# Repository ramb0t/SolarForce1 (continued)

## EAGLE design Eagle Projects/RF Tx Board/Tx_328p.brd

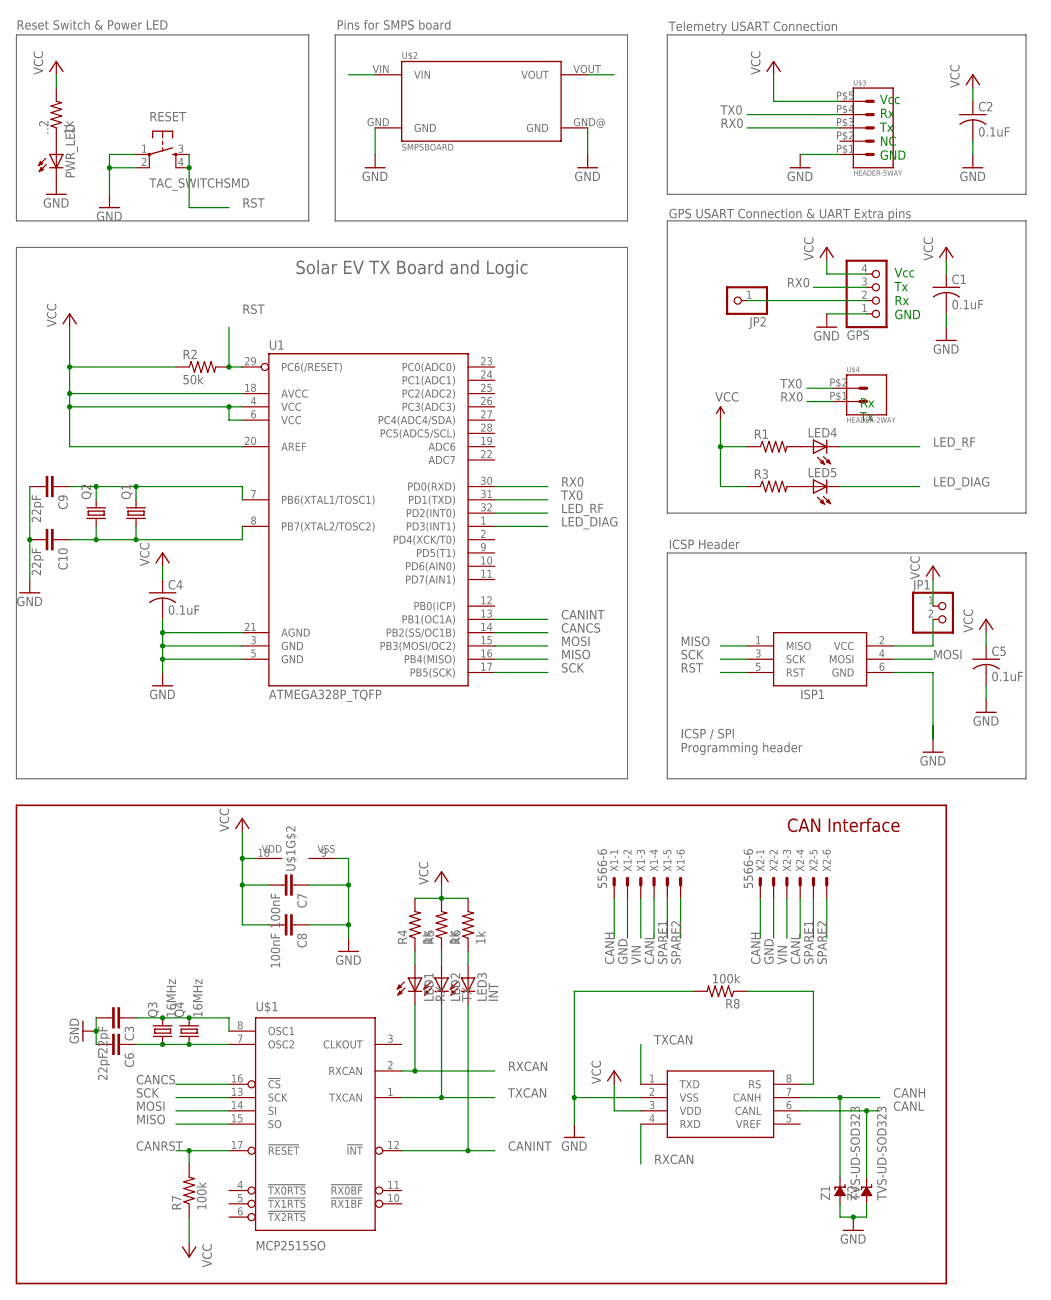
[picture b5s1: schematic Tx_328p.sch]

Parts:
..2: 1k; M0805
C1, C2, C4, C5: 0.1uF; C0805
C3, C6, C9, C10: 22pF; C0805K
C7, C8: 100nF; C0805K
GPS: PINHD-1X4; 1X04
ISP1: AVRISP-BOX
JP1: PINHD-1X2; 1X02
JP2: PINHD-1X1; 1X01
LED1: RX; CHIP-LED0805
LED2: TX; CHIP-LED0805
LED3: INT; CHIP-LED0805
LED4, LED5: LEDSML0805; SML0805
PWR_LED: LEDCHIP-LED0805; CHIP-LED0805
Q1: CRYSTALHC49S; HC49/S
Q2: CRYSTALSM49; SM49
Q3: 16MHz; HC49/S
Q4: 16MHz; HC49UP
R1, R3: R-US_M0805; M0805
R2: 50k; M0805
R4, R5, R6: 1k; R0805
R7, R8: 100k; R0805
RESET: TAC_SWITCHSMD; TACTILE-SWITCH-SMD
U1: ATMEGA328P_TQFP; TQFP32-08
U2: MCP2551; SO08
U$1: MCP2515SO; SO-18W
U$2: SMPSBOARD
U$3: HEADER-5WAY; 1744426-5
U$4: HEADER-2WAY; 1744426-2
X1, X2: 5566-6
Z1, Z2: TVS-UD-SOD323; SOD323

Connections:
CANCS: U1.14 (PB2(SS/OC1B)), U$1.16 (!CS)
CANH: U2.7 (CANH), X1.1, X2.1, Z1.C
CANINT: LED3.C, U1.13 (PB1(OC1A)), U$1.12 (!INT)
CANL: U2.6 (CANL), X1.4, X2.4, Z2.C
CANRST: R7.2, U$1.17 (!RESET)
CANSTBY: R8.1, U2.8 (RS)
GND: C1.2, C2.2, C3.2, C4.2, C5.2, C6.2, C7.1, C8.1, C9.2, C10.2, GPS.1, ISP1.6 (GND), PWR_LED.C, R8.2, RESET.1, RESET.2, U1.3 (GND), U1.5 (GND), U1.21 (AGND), U2.2 (VSS), U$1.9 (VSS), U$2.GND, U$2.GND@ (GND), U$3.P$1, X1.2, X2.2, Z1.A, Z2.A
LED_DIAG: LED5.C, U1.1 (PD3(INT1))
LED_RF: LED4.C, U1.32 (PD2(INT0))
MISO: ISP1.1 (MISO), U1.16 (PB4(MISO)), U$1.15 (SO)
MOSI: ISP1.4 (MOSI), U1.15 (PB3(MOSI/OC2)), U$1.14 (SI)
unnamed: C9.1, Q1.2, Q2.2, U1.7 (PB6(XTAL1/TOSC1))
unnamed: C10.1, Q1.1, Q2.1, U1.8 (PB7(XTAL2/TOSC2))
unnamed: GPS.2, JP2.1
unnamed: LED4.A, R1.2
unnamed: LED5.A, R3.2
unnamed: ..2.1, PWR_LED.A
unnamed: LED1.A, R4.1
unnamed: LED2.A, R5.1
unnamed: LED3.A, R6.1
unnamed: C3.1, Q3.2, Q4.2, U$1.8 (OSC1)
unnamed: C6.1, Q3.1, Q4.1, U$1.7 (OSC2)
unnamed: ISP1.2 (VCC), JP1.2
RST: ISP1.5 (RST), R2.2, RESET.3, RESET.4, U1.29 (PC6(/RESET))
RX0: GPS.3, U1.30 (PD0(RXD)), U$3.P$3, U$4.P$1
RXCAN: LED1.C, U2.4 (RXD), U$1.2 (RXCAN)
SCK: ISP1.3 (SCK), U1.17 (PB5(SCK)), U$1.13 (SCK)
SPARE1: X1.5, X2.5
SPARE2: X1.6, X2.6
TX0: U1.31 (PD1(TXD)), U$3.P$4, U$4.P$2
TXCAN: LED2.C, U2.1 (TXD), U$1.1 (TXCAN)
VCC: ..2.2, C1.1, C2.1, C4.1, C5.1, C7.2, C8.2, GPS.4, JP1.1, R1.1, R2.1, R3.1, R4.2, R5.2, R6.2, R7.1, U1.4 (VCC), U1.6 (VCC), U1.18 (AVCC), U1.20 (AREF), U2.3 (VDD), U$1.18 (VDD), U$2.VOUT, U$3.P$5
VIN: U$2.VIN, X1.3, X2.3

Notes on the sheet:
Vcc Rx Tx NC GND
Vcc Tx Rx GND
Rx Tx
ICSP / SPI Programming header
Reset Switch & Power LED
Pins for SMPS board
Telemetry USART Connection
GPS USART Connection & UART Extra pins
ICSP Header
Solar EV TX Board and Logic
CAN Interface

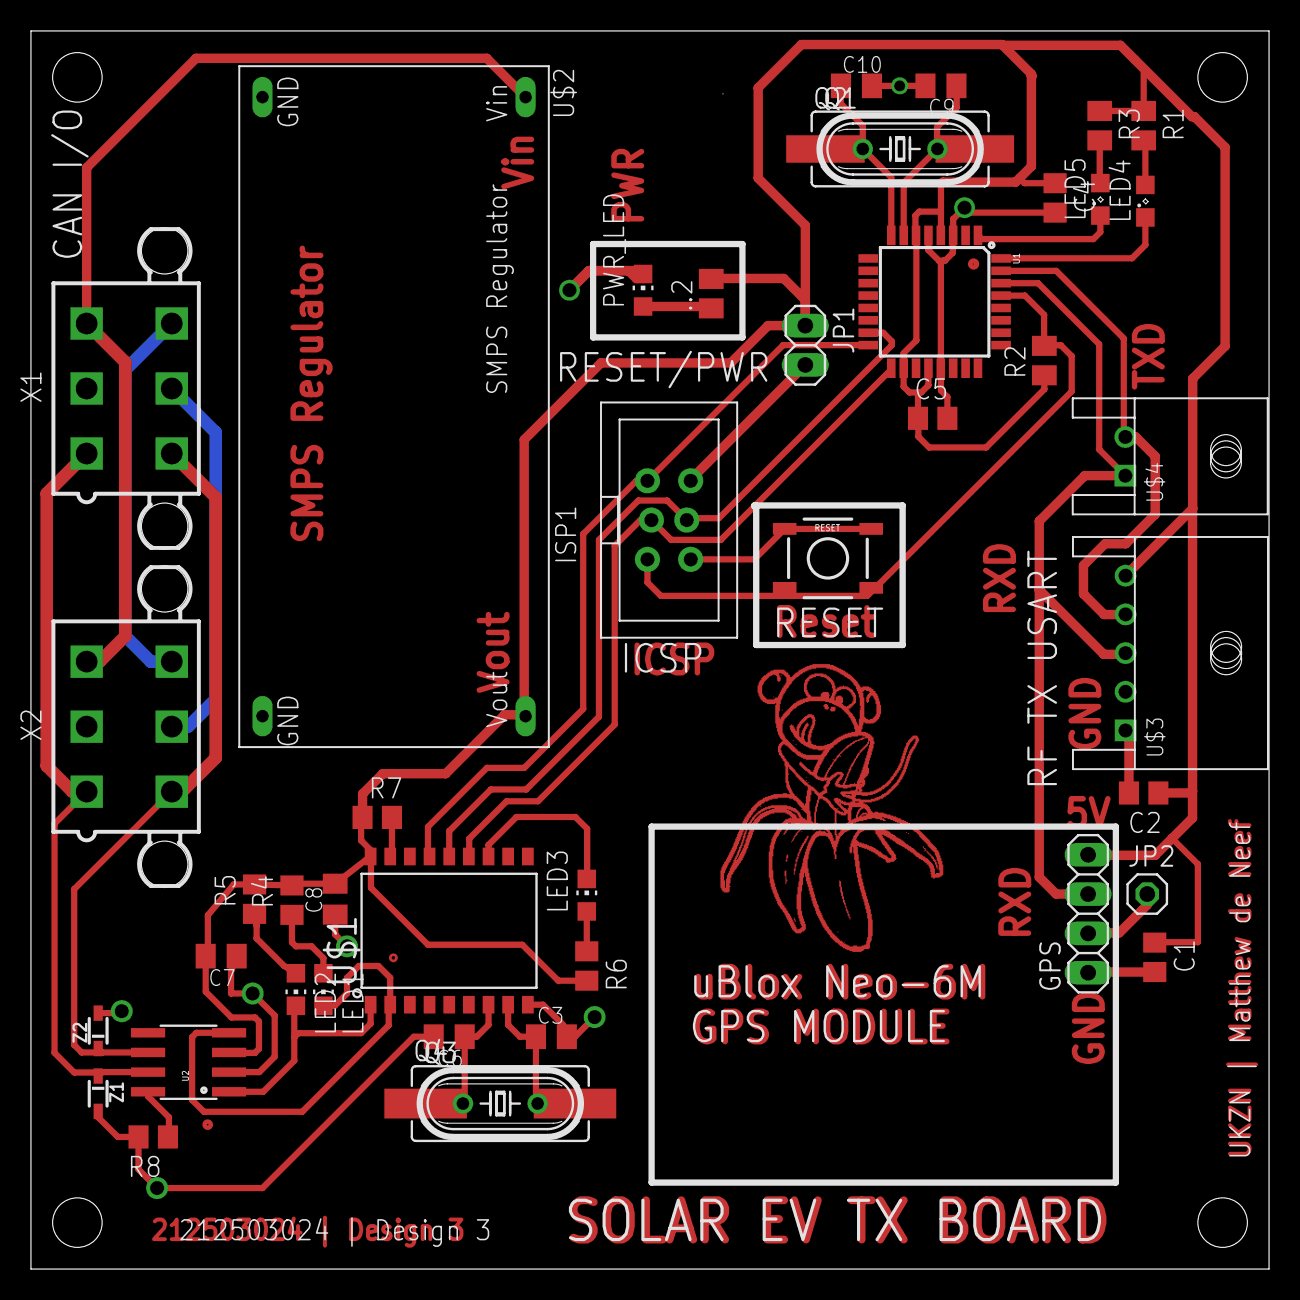
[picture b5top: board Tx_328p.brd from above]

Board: 2 copper layers, 80.0 x 80.0 mm, 44 parts (0 on the bottom side), 33 nets.

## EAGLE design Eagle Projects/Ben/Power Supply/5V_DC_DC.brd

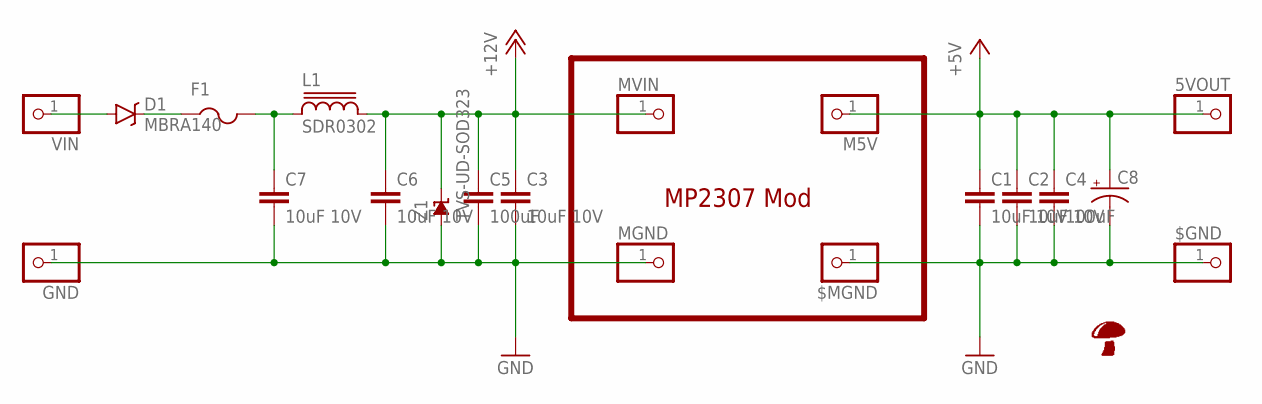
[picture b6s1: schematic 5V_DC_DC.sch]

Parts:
5VOUT: PINHD-1X1; 1X01
$GND: PINHD-1X1; 1X01
$MGND: PINHD-1X1; 1X01
C1, C2, C3, C6, C7: 10uF 10V; C0805
C4, C5: 100uF; C1206
C8: CPOL-USD; PANASONIC_D
D1: MBRA140; SMA-DIODE
F1: PTCFUSE-1812; 1812
GND: PINHD-1X1; 1X01
L1: SDR0302
M5V: PINHD-1X1; 1X01
MGND: PINHD-1X1; 1X01
MVIN: PINHD-1X1; 1X01
U$1: SHROOM5MM; SHROOM
VIN: PINHD-1X1; 1X01
Z1: TVS-UD-SOD323; SOD323

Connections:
+5V: 5VOUT.1, C1.1, C2.1, C4.1, C8.+, M5V.1
+12V: C3.1, C5.1, C6.1, L1.2, MVIN.1, Z1.C
GND: $GND.1, $MGND.1, C1.2, C2.2, C3.2, C4.2, C5.2, C6.2, C7.2, C8.-, GND.1, MGND.1, Z1.A
unnamed: C7.1, F1.2, L1.1
unnamed: D1.C, F1.1
unnamed: D1.A, VIN.1

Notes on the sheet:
MP2307 Mod

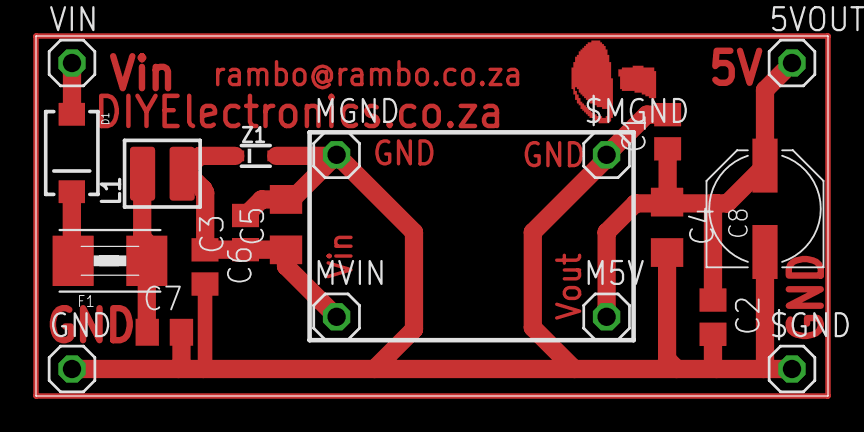
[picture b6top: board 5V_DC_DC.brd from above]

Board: 2 copper layers, 44.0 x 20.0 mm, 21 parts (0 on the bottom side), 6 nets.

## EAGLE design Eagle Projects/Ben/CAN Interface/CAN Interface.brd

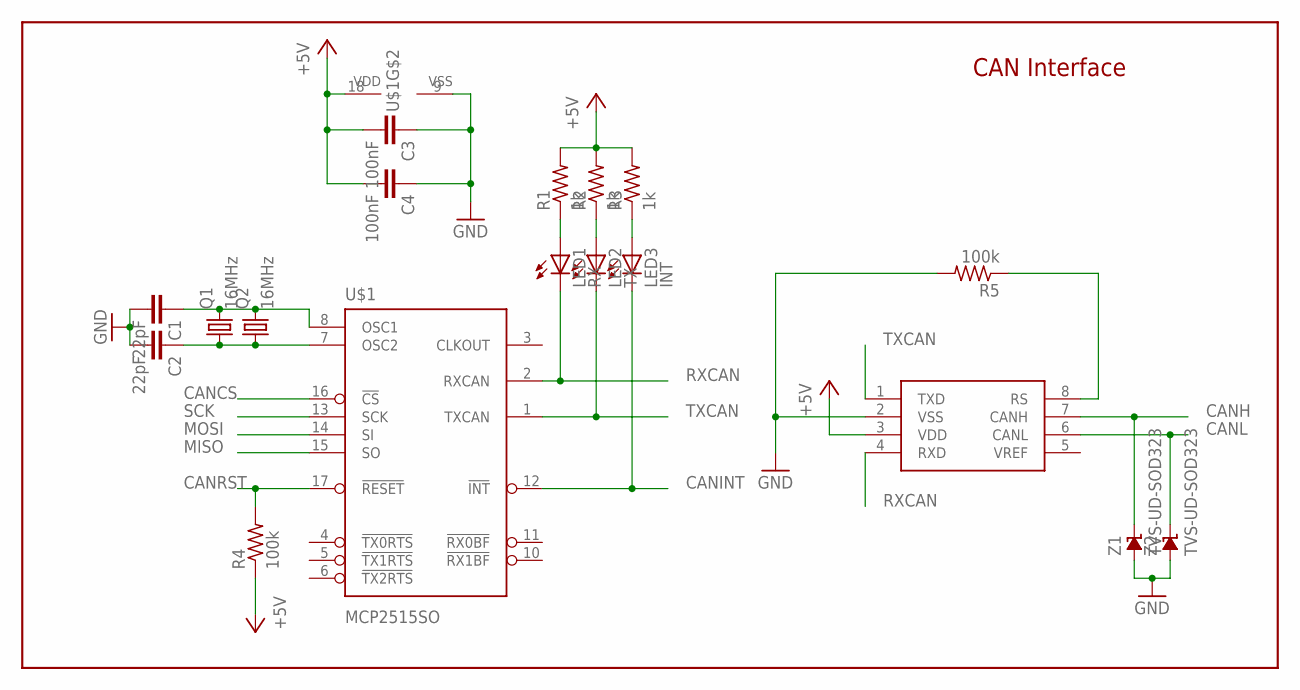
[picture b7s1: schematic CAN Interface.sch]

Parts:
C1, C2: 22pF; C0805K
C3, C4: 100nF; C0805K
LED1: RX; CHIP-LED0805
LED2: TX; CHIP-LED0805
LED3: INT; CHIP-LED0805
Q1: 16MHz; HC49/S
Q2: 16MHz; HC49UP
R1, R2, R3: 1k; R0805
R4, R5: 100k; R0805
U1: MCP2551; SO08
U$1: MCP2515SO; SO-18W
Z1, Z2: TVS-UD-SOD323; SOD323

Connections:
+5V: C3.2, C4.2, R1.2, R2.2, R3.2, R4.1, U1.3 (VDD), U$1.18 (VDD)
CANCS: U$1.16 (!CS)
CANH: U1.7 (CANH), Z1.C
CANINT: LED3.C, U$1.12 (!INT)
CANL: U1.6 (CANL), Z2.C
CANRST: R4.2, U$1.17 (!RESET)
CANSTBY: R5.1, U1.8 (RS)
GND: C1.2, C2.2, C3.1, C4.1, R5.2, U1.2 (VSS), U$1.9 (VSS), Z1.A, Z2.A
MISO: U$1.15 (SO)
MOSI: U$1.14 (SI)
unnamed: C2.1, Q1.1, Q2.1, U$1.7 (OSC2)
unnamed: C1.1, Q1.2, Q2.2, U$1.8 (OSC1)
unnamed: LED1.A, R1.1
unnamed: LED2.A, R2.1
unnamed: LED3.A, R3.1
RXCAN: LED1.C, U1.4 (RXD), U$1.2 (RXCAN)
SCK: U$1.13 (SCK)
TXCAN: LED2.C, U1.1 (TXD), U$1.1 (TXCAN)

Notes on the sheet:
CAN Interface

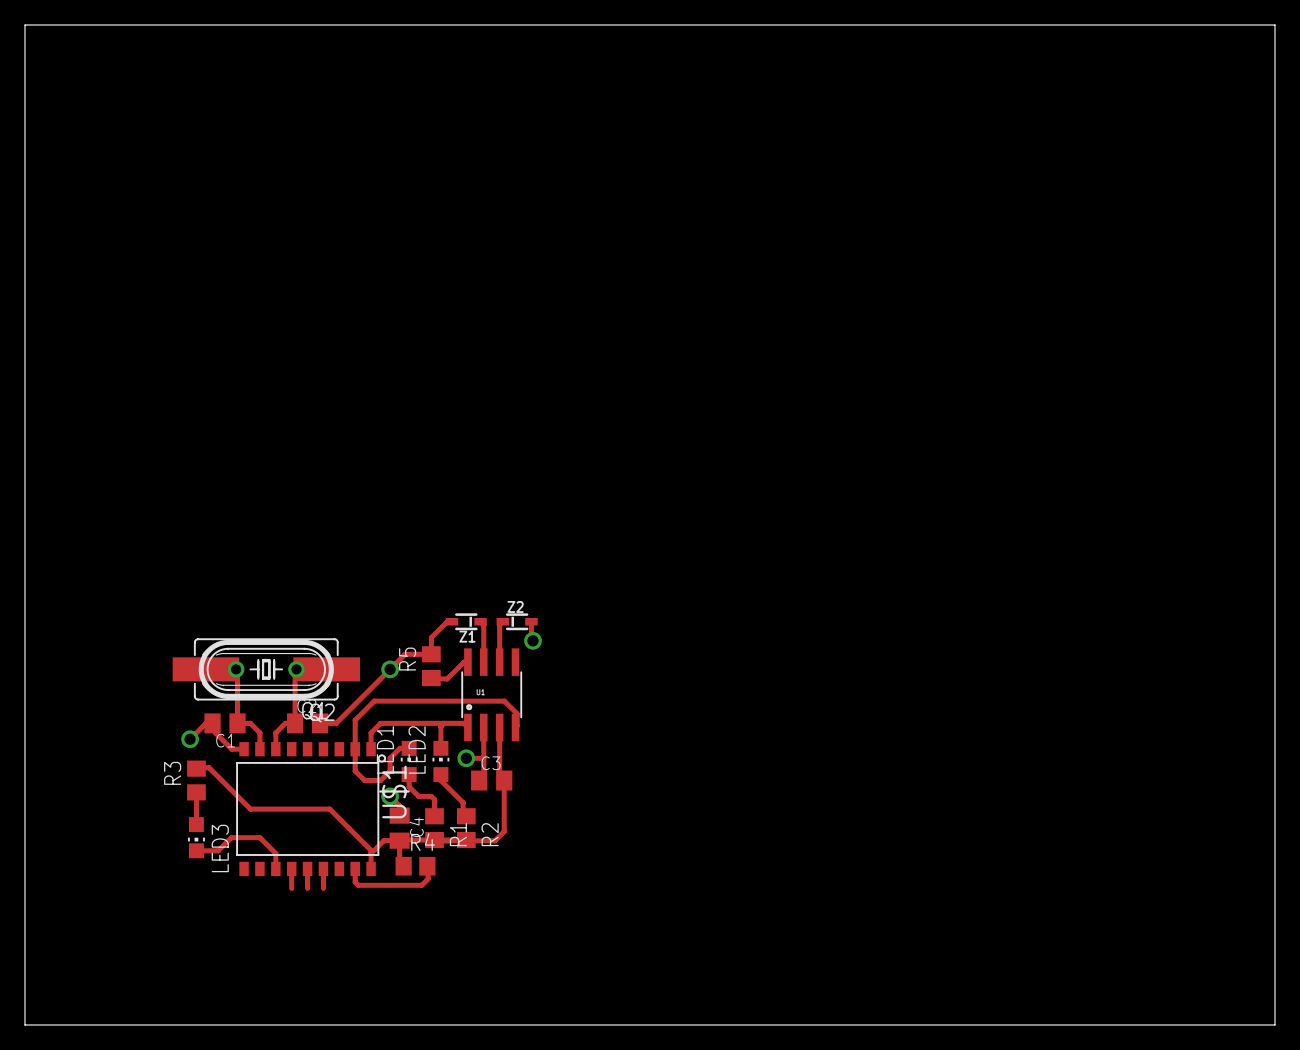
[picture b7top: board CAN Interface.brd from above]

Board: 2 copper layers, 100.0 x 80.0 mm, 18 parts (0 on the bottom side), 14 nets.

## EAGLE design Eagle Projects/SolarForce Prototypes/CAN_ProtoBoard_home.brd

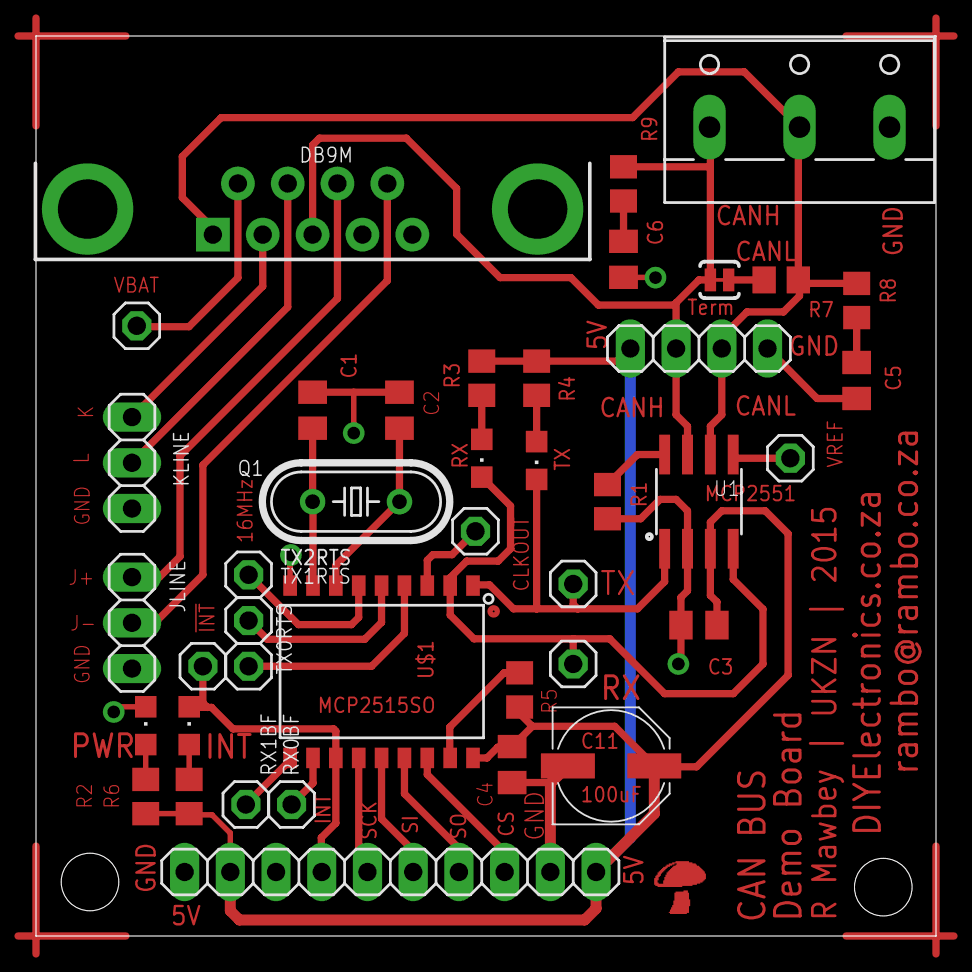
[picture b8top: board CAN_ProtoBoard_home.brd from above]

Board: 2 copper layers, 50.0 x 50.0 mm, 41 parts (0 on the bottom side), 34 nets.

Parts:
!INT: 1X01
C1, C2: 22pF; C0805K
C3, C4: 100nF; C0805K
C5, C6: 560pF; C0805K
C11: 100uF; PANASONIC_D
CAN: 1X04
CANSCREW: W237-103
CLKOUT: 1X01
DB9M: DB9_MALE
IO: 1X10
JLINE: 1X03
KLINE: 1X03
LED1: PWR; CHIPLED_0805
LED2: RX; CHIPLED_0805
LED3: TX; CHIPLED_0805
LED4: INT; CHIPLED_0805
Q1: 16MHz; HC49/S
R1, R2: R0805
R3, R4, R6: 1k; R0805
R5: 10k; R0805
R7: 120E; R0805
R8, R9: 100E; R0805
RX, RX0BF, RX1BF: 1X01
SJ1: Term; SJ_2S-TRACE
TX, TX0RTS, TX1RTS, TX2RTS: 1X01
U1: MCP2551; SO08
U$1: MCP2515SO; SO-18W
VBAT: 1X01
VREF: 1X01

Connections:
+5V: C3.1, C4.1, C11.+, CAN.4, IO.2, IO.10, R2.2, R3.2, R4.2, R5.2, R6.2, U1.3, U$1.18
CANH: CAN.3, CANSCREW.1, DB9M.3, R9.2, SJ1.1, U1.7
CANL: CAN.2, CANSCREW.2, DB9M.5, R7.2, R8.2, U1.6
CLKOUT: CLKOUT.1, U$1.3
CS: IO.8, U$1.16
GND: C1.1, C2.1, C3.2, C4.2, C5.1, C6.1, C11.-, CAN.1, CANSCREW.3, DB9M.2, IO.1, IO.9, JLINE.1, KLINE.1, LED1.C, R1.2, U1.2, U$1.9
INT: !INT.1, IO.4, LED4.C, U$1.12
J+: DB9M.7, JLINE.3
J-: DB9M.6, JLINE.2
K: DB9M.4, KLINE.3
L: DB9M.8, KLINE.2
unnamed: C1.2, Q1.2, U$1.8
unnamed: C2.2, Q1.1, U$1.7
unnamed: LED2.A, R3.1
unnamed: LED3.A, R4.1
unnamed: R5.1, U$1.17
unnamed: LED1.A, R2.1
unnamed: LED4.A, R6.1
unnamed: R1.1, U1.8
unnamed: R7.1, SJ1.2
unnamed: U1.5, VREF.1
unnamed: C5.2, R8.1
unnamed: C6.2, R9.1
RX0BF: RX0BF.1, U$1.11
RX1BF: RX1BF.1, U$1.10
RXCAN: LED2.C, RX.1, U1.4, U$1.2
SCK: IO.5, U$1.13
SI: IO.6, U$1.14
SO: IO.7, U$1.15
TX0RTS: TX0RTS.1, U$1.4
TX1RTS: TX1RTS.1, U$1.5
TX2RTS: TX2RTS.1, U$1.6
TXCAN: LED3.C, TX.1, U1.1, U$1.1
VBAT: DB9M.9, VBAT.1

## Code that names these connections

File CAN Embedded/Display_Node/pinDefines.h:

/*
 * pinDefines.h
 *
 *  Created on: 04 Apr 2015
 *      Author: RobThePyro
 */

#ifndef PINDEFINES_H_
#define PINDEFINES_H_

#define LCD_PWM_DDR		DDRB
#define LCD_PWM_PORT	PORTB
#define LCD_PWM_PIN		PINB
#define LCD_PWM 		PB1

#define LCD_SCKCTL_DDR	DDRD
#define LCD_SCKCTL_PORT	PORTD
#define LCD_SCKCTL_PIN	PIND
#define LCD_SCKCTL 		PD6

#define LED_DDR			DDRD
#define LED_PORT		PORTD
#define LED_RF			PD0
#define LED_B			PD1
#define LED_ON(led)		LED_PORT |= (1<<led)
#define LED_OFF(led)	LED_PORT &= ~(1<<led)
#define LED_FLIP(led)	LED_PORT ^= (1<<led)

#define BTN_DDR			DDRD
#define BTN_PORT		PORTD
#define BTN_PIN			PIND
#define BTN_1			PD2
#define BTN_2			PD3
#define BTN_3			PD4
#define BTN_4			PD5

#define CRUISE_PWM_DDR	DDRD
#define CRUISE_PWM 		PD3  //Use Timer2 -> OSC2B Pin for PWM for motor control?

#define CRUISE_ADC_DDR	DDRC
#define CRUISE_ADC_PORT	PORTC
#define CRUISE_ADC_PIN	PINC
#define CRUISE_ADC_THR 	PC0	 //Throttle on PC0 / ADC0 ?
#define CRUISE_ADC_THR_MUX	0





#endif /* PINDEFINES_H_ */

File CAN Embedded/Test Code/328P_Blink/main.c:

/*
 * main.c
 *
 *  Created on: 08 Apr 2015
 *      Author: RobThePyro
 */


#include <avr/io.h>
#include <util/delay.h>

#define LED_DDR		DDRD
#define LED_PORT	PORTD
#define LED1		PD3
#define LED2		PD2
#define LEDT_DDR		DDRC
#define LEDT_PORT	PORTC
#define LEDT1		PC2
#define LEDT2		PC3

int main(void){
	// setup leds
	LED_DDR |= (1<<LED1)|(1<<LED2);
	LEDT_DDR |= (1<<LEDT1)|(1<<LEDT2);

	while(1){
		// toggle
		LED_PORT |= (1<<LED1);
		LED_PORT &= ~(1<<LED2);
		LEDT_PORT |= (1<<LEDT1);
		LEDT_PORT &= ~(1<<LEDT2);
		_delay_ms(500);

		LED_PORT |= (1<<LED2);
		LED_PORT &= ~(1<<LED1);
		LEDT_PORT |= (1<<LEDT2);
		LEDT_PORT &= ~(1<<LEDT1);
		_delay_ms(500);
	}


}

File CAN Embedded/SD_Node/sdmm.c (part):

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

#define DO_INIT()					/* Initialize port for MMC DO as input */
#define DO			(PINB &	(1<<PB4))	/* Test for MMC DO ('H':true, 'L':false) */

#define DI_INIT()	DDRB  |= (1<<PB3)	/* Initialize port for MMC DI as output */
#define DI_H()		PORTB |= (1<<PB3)	/* Set MMC DI "high" */
#define DI_L()		PORTB &= ~(1<<PB3)	/* Set MMC DI "low" */

#define CK_INIT()	DDRB  |= (1<<PB5)	/* Initialize port for MMC SCLK as output */
#define CK_H()		PORTB |= (1<<PB5)	/* Set MMC SCLK "high" */
#define	CK_L()		PORTB &= ~(1<<PB5)	/* Set MMC SCLK "low" */

#define CS_INIT()	DDRB  |= (1<<PB1)	/* Initialize port for MMC CS as output */
#define	CS_H()		PORTB |= (1<<PB1)	/* Set MMC CS "high" */
#define CS_L()		PORTB &= ~(1<<PB3)	/* Set MMC CS "low" */


static
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
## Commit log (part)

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2015-02-21 Started first project
2015-02-21 Added folders for each project ?
2015-02-21 Test code from online site:
    *Basic MCU to MCP SPI Comms
    *Atmel Studio project form
2015-02-21 Initial Concept GUI for Telemetry System
    *Resources for images in directory
    *Next update to include graph view accessible from menu switcher
    *Feel free to edit
2015-02-21 Code running on mcu and working for can Tx test!!
2015-02-21 Rx Code not working atm..
2015-02-22 Changed what files are tracked due to VS bullshite
2015-02-24 No functionality added yet, just checking I can push now
2015-02-26 Did some initial work with lcd.. not working yet.
2015-02-27 Started work on CAN PCB
2015-02-28 Used wrong package for MCP2515.. SO not TSSOP!! Changed and fixxed...
2015-03-03 Working on protopanels
2015-03-04 DatabaseFiddling now has some fiddling.
    creation of XML file via console successful, checks not overwriting existing file.
    Next up: writing entries to XML file.
2015-03-05 Modified to use LINQ
    Node addition code is executing; but not writing to the XML file for some reason.
2015-03-05 cleaned up code a little and added comments.
    next up: performing basic queries >> and how to make them flexible!
2015-03-07 Now have node attributes.
2015-03-07 Simple routines for Arduino *Serial comms for RF *Serial test for GPS
2015-03-10 Basic Comms "Ground unit on COM4 sends data through terminal *Data received by remote unit and read out on terminal in COM3
2015-03-15 CAN Rx test code now working. flashes led!!
2015-03-18 [Arduino] Working Code for GPS-> PC serial logging across RF link *Deleted extra code *Left test routines for diagnostics
2015-03-21 Proof of Concept Code:
    Database:
    -XML file generation
    -add entries
    -query/mine database
    Data Flow Tools:
    -Multi-Threading
2015-03-21 GFX LCD working!
2015-03-21 XML File with MAVLink definitions for Solar Car - Use mavlink_generator for this - entire Python script and files available at https://github.com/zhao0079/mavlinkgen
2015-03-21 Full MAVLink Generator Repo - Allows modifying XML for MAVLink frames - Creates an entire C-structs headers folder from an XML - these headers can run on MCUs - Run ~/mavgen.py to choose XML file to 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
2015-03-21 GFX LCD test node now working :D
2015-03-22 XML Recompile II - Added Gyro/Accello Forgot to add the actual XML file...here it is!
2015-03-23 Did some work on display node eagle
2015-03-29 Mucking around with LCDs
2015-03-29 [MAVLink] Miscellanous Additions *Sends heartbeat to QGroundControl with MAVlink *Revised SolarCarFINAL library with all int values *extra Arduino files for GPS tests
2015-03-29 Don't mind me here, just breakin tings.
2015-03-29 Working on MCP2515 library
2015-03-30 Initial AVR Solution with MAVLink includes *Rewritten in embedded C *Working on serial comms (Getting garbage atm @ right baud) *Has heartbeat function code
2015-03-30 32u4 File is now a thing.
    However, there is no code there yet (but things are still things)
2015-03-30 [MAVLink] Some more edits: *Heartbeat basic working *UART Library
2015-03-30 Just catching up
2015-03-30 Some more work on CAN 'library'
2015-03-31 More EAGLE *Not sure which pin headers? *PDIP or SMD for MCU and if so which layout, as 328p SMD types pinouts seem to differ *Everything needed is connected (i think)
2015-03-31 just a commit so we can all merge nicely
2015-03-31 EAGLE additions *modularise connectors (Thanks Ben :P)
2015-03-31 Hall Effect code so far
2015-03-31 prototype code on atmega32 is now included. Still working on efficient connection-orientated comms.
2015-03-31 More edits *ISR functionality active *Using Ben's linked CAN libraries now
2015-03-31 in case
2015-03-31 Test
2015-03-31 Prototype CAN receving! [test] *CAN interface definitions *Print CAN data to UART *Also GPS & MAVLink heartbeat
2015-03-31 Working CAN Rx & send via UART on RF *Receive CAN from bus *Parse GPS data *generate MAVLink -->Send all over RF to serial via Wireless
2015-03-31 Can Rx Conditionals: *Displays errors if Init fails *Displays error if CAN controller error *Displays msg if no data bits *Shows if msg RTR / not
2015-03-31 Started Display Node and SD Node code bases
2015-04-01 Display Node Compiling
2015-04-01 TerayKrayKray
2015-04-01 TeRayKrayKray fixxed.
2015-04-01 Tweaks for debugging stuff
2015-04-01 confirmed test
2015-04-01 More Tweaks for proper logging
2015-04-01 Working!
2015-04-01 Changed the UART library to a modified one with an available() and flush() function. Matt this breaks your delay code, soz
2015-04-02 GPS Code tweaks (tired to think :P)
2015-04-02 uart fixxed?
2015-04-02 Test code in a state ready for the BMS ? Maybe!
2015-04-03 Added Tx/Rx LEDs for board + measurements of GPS & RF boards for comparison *cough*Autorouted *cough* and still broken, redoing manually :P
2015-04-03 Many things, most notably the Rx schematic
    I just put headers for the RF transceiver going to Tx/Rx, because I'm not 100% sure how that's connecting - I just know it uses the UART
2015-04-03 Power Supply Module Done
2015-04-03 Some routing done on Tx board
2015-04-03 GND plane for patel
2015-04-03 Eagle Library RobThePyro with SMPS part added
2015-04-04 Small change to library pin display
2015-04-04 Almost lost some important stuff! managed to save it :D
2015-04-04 Birds Tweeting. Shit. Bed Time..
2015-04-04 There is now a PCB for the Rx board. Comments and criticism welcome.
2015-04-04 Added homebrew TE Connectivity EP 2.5mm TPA Connector series. Only right angle for now..
2015-04-04 Display node nearly done
2015-04-04 Sorted Matts Board :)
2015-04-04 Working On Protection
2015-04-04 Working on boards and moar code...
2015-04-04 Cleaned up code (will add new code tomorrow): *Modular send/receive CAN/GPS/UART functions
2015-04-04 Rx Rev 2 updated: now with Tx,Rx,Vcc,Gnd in one place for the RF board.
    This entire piece of hardware is currently reliant on the USB to supply power. This isn't a problem, right?
2015-04-05 fixed up patels board :D
2015-04-05 Display Node Done?
2015-04-05 final rx board (i think) is still called rev2 xD
    on other side, minor software tweaks but they're nonfunctional atm
2015-04-05 Potato!
2015-04-05 Exported BMP's
2015-04-05 Kinda-Working GPS GPRMC parsing by 1st-principles
2015-04-05 Fixed n00b mistake on board+Schematic for Tx board
2015-04-05 a commit.
2015-04-06 Small refractor for readability
2015-04-06 MPU almost happy
2015-04-06 Fixed my silly on matts board
2015-04-07 fixed some T things/
2015-04-07 Speedy
2015-04-08 Done
2015-04-08 Some unresolved exceptions in the COM Port setup, but shouldn't be able to cause crashes.
    XML writing works manually.
    XML queries work with some hard-coded implementations. Designing Zedgraph Form and doing implementation atm.
2015-04-09 Fixed patties board
2015-04-10 Found some float defs; Recompiled Mavlink Headers
    *No more floats!
    *Refactoring code for clarity
    *Next get functionality back (lol)
2015-04-11 Working on code and things
2015-04-11 Working
2015-04-11 Display node inital code working!!
2015-04-12 BMS emulator working?
2015-04-12 Solar Car XML update
2015-04-12 Thingies
2015-04-12 Send/Receive MAVLink On loopback *New convenience functions to send MAVLink packets
2015-04-12 Added pin Int0 stuff to CAN library
2015-04-12 Display Stable with some very hackish code?
2015-04-13 Things are getting weeeird...
2015-04-13 some nice text file things. working on demo.
2015-04-13 Errors gone but convenience fns aren't sending actual data
2015-04-14 *Fixed convenience functions *Wrote new bridge header adaptor file *Implementing convenience-decoding soon
2015-04-14 Code trimming, working on decode - loopback, but no RAM on one 328p for all that xD
2015-04-15 Code for receiver MCU (solution + all MAV headers again, sorry) *decoding sorta working (decodes heartbeat so long)
2015-04-16 Added CAN Database
2015-04-16 MATT SAID HI!!
2015-04-16 Hack internet job using weakest internet in the world
2015-04-16 More definitions and decoding code in comma delimited form
2015-04-17 Test Node Raw Listen mode updated to use buffer
2015-04-17 Working on the CAN db thing
2015-04-17 Terayza Input Capture Code Help
2015-04-17 The database is now literate.
2015-04-17 Stuff fixed for proper sending of frames
2015-04-17 Started Cadding Things
2015-04-18 RX board fixes mainly-> removed garbage between messages *Added more RX msg definitions *Tweaked IDs for messages *Conditional prototype error checking
2015-04-18 Display starting to get there... Want to play around with the buffer now. Likely going to break stuff! xD
2015-04-18 Some fixes (managed to break it all day :/ only working again now...still got GPS to go!)
2015-04-18 working on test node state machine
2015-04-18 more GPS things
2015-04-18 Just incase things go boom! :P
2015-04-18 I dont even...
2015-04-18 STABLE display code... Power just needs to be fixed
2015-04-18 Some edits to the querying structure and testing with a uc simulating MavLink input (that was quite inaccurate, so I scrapped it)
    Database storage of different values seems to work, updating seems solid, graphing and sensor combobox population still intact.
    Weird things happen if queries are made to a db with no entries. Working on a fix.
2015-04-19 Fixed the power display code
2015-04-19 extended some functionality and resolved an intermittent error in the Connect to COM Port screen.
2015-04-19 Will Source Tree finally update?!
2015-04-19 Database now closes off correctly before closing.
    Solar Motion Tab now shows the Hall Effect & Motor Driver Speeds. Summary shows the Motor Driver Speed.
2015-04-19 GRAPHS! in-car testing, graphs from GUI saved to repo
    minor other gui mods
2015-04-20 Added individual CAN containers for each component to avoid garbage being loaded from other IDs like today!
2015-04-20 last commit didn't fix things... i think I manually got everything back to the way it was. Would like to test though! (there is a good code commit earlier on to roll back to, if needed)
2015-04-20 CAN Message Routine Receive Overhaul *Using Ben's Display Node style CAN msg retrieval *Interrupt-based case statements with separate objects *Definitions on what's stored where
2015-04-20 [NOT TESTED YET] MAVLink send functions map CAN received data to fields
2015-04-20 More fixies?
2015-04-20 Maddness
2015-04-20 Some Updates to codebase
2015-04-21 Fixed Matts dodgy commit?
2015-04-21 uh yea you like that speed reading don't you?!
2015-04-21 Some Tx side tweaks , working on Rx next then test with CAN
2015-04-21 Mr Hall Sensors turn
2015-04-21 Added new warning notifications implementation & functionality. Added some error checking and code robustness things. Removed superfluous variables that just wasted memory (even if this isn't a micro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
2015-04-24 committing so i can checkout something else. THIS IS NOT WORKING PROPERLY!!!!
2015-04-24 Random commit, trying to fix CAN receive and proper sending
2015-04-24 in the middle of strange stories... a wild commit appeared
2015-04-24 Files exist for interrupts stuff, more modularising....
2015-04-25 Strangeness...but ISR-based HB sending now
2015-04-25 Conditional sending code for MAVLink objects added
2015-04-25 *Fixed MAV Send ISR stuffs *Fixed conditional MAV sending routine *Sorted flag stuff
2015-04-25 BMS Database file completed
2015-04-25 database thing
2015-04-25 Final tweaks to DB and msg defs for Tx
2015-04-25 Revised MAVLink library files with new defs
2015-04-25 I dunno what I have done, but I've been having lots of fun #rhymeTime
2015-04-25 RX routines adjusted
2015-04-25 dunno
2015-04-25 Things
2015-04-26 Sending variable speed getting along
2015-04-26 Gyro knows how to send CAN! HOLY MOLY!
2015-04-26 *BMS Rx speed from CAN improved, getting more msgs *Speed reading OK *Restructured RX board routines
2015-04-26 GPS sends in plaintext but works
2015-04-26 only uart library seems grumpy. isolating and working on it
2015-04-26 Test Node Sorted?
2015-04-26 Sending correct Speed stuff 100%
2015-04-26 Display node commit for matt
2015-04-26 Accello gyro CAN Rx routines and RX board routines
2015-04-26 Updated accello/gyro MAVLink RX side file
2015-04-26 Sending all nicely, mpu pull out still a problem
2015-04-26 Test node MPPT stuff mod. Doesnt crash.. YET. DUN DUN DUN
2015-04-26 WORKING MPU with origional I2C lib, doesnt CAN when removed
2015-04-26 Changed the CAN library back.. use #define UART_RX_BUFFER to change the buffer size
2015-04-26 Display modded to display MPPT on a new screen? effective? Bugs? Can crash? unknown. NEED TO TEST YO. #YOLO SWAG
2015-04-27 Activated all the sending functions (whether they work is another story)
2015-04-27 Added display backlight control and button press stuff
2015-04-27 More Fixes
2015-04-27 Ben's gliffy pic
2015-06-24 **No code functionality changes** >>MAVLink Tx board code library --------------------------------------------------- *Commented some code *Added intro blurbs to some functions *Added warnings for au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
2015-07-03 Commit Tiem
2015-07-04 MPPT stuff working?
2015-07-04 Working on car today. MPPT stuff a winner!
2015-07-05 basic pwm feedthrough
2015-07-08 Experimenting with ideas...
2015-09-07 Working on the mavlink stuff
